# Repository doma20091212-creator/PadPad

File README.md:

#  PadPad
A simple macropad built for stardance mission, consists of 5 key switches, a rotary encoder and uses Seeduino XIAO RP2040.
It utilizies Direct Pins instead of Keyboard Matrix.

## Dimensions

PCB Dimensions: 65mm x 64mm
Case Dimensions: 84.90mm x 84.50mm x 16mm

## BOM

- 5x Cherry MX 1.00u Switches
- 1x Rotary encoder with switch
- 1x Seeduino XIAO RP2040
- PCB Fabrication
- 3D Printing

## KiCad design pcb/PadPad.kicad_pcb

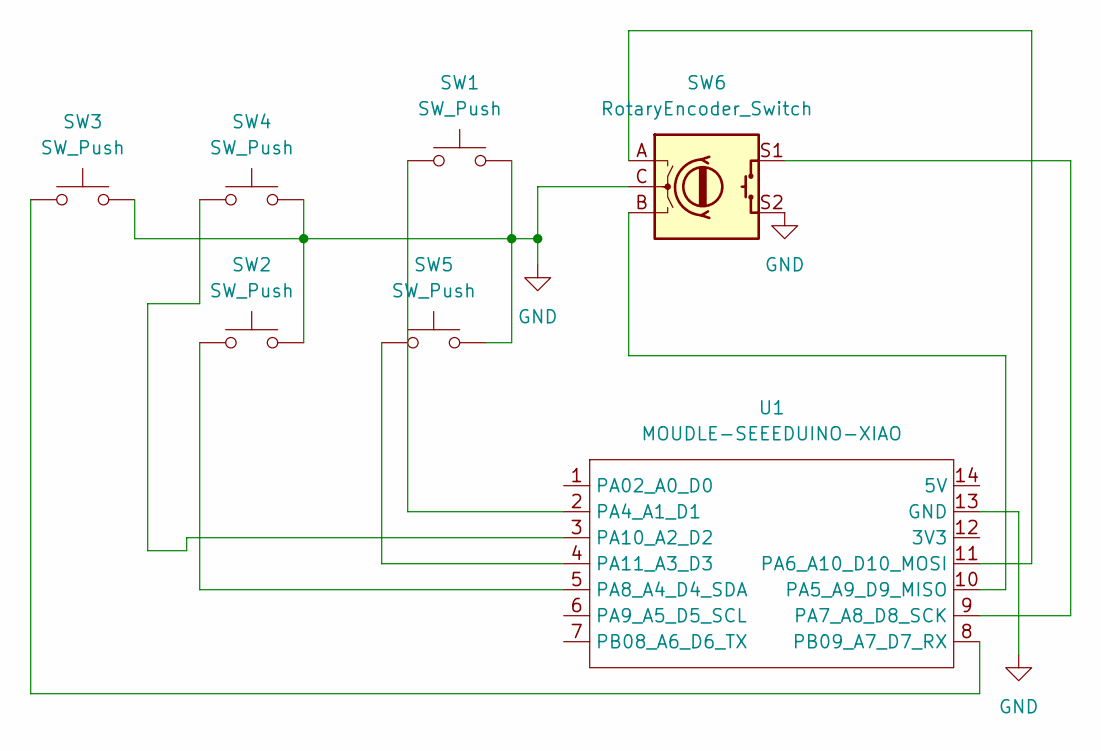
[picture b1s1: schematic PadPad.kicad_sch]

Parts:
SW1, SW2, SW3, SW4, SW5: SW_Push; SW_Cherry_MX_1.00u_PCB
SW6: RotaryEncoder_Switch; RotaryEncoder_Alps_EC11E-Switch_Vertical_H20mm
U1: MOUDLE-SEEEDUINO-XIAO; XIAO-Generic-Hybrid-14P-2.54-21X17.8MM

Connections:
GND: SW1.2, SW2.2, SW3.2, SW4.2, SW5.2, SW6.C, SW6.S2, U1.13 (GND)
unnamed: SW1.1, U1.2 (PA4_A1_D1)
unnamed: SW6.B, U1.10 (PA5_A9_D9_MISO)
unnamed: SW6.A, U1.11 (PA6_A10_D10_MOSI)
unnamed: SW6.S1, U1.9 (PA7_A8_D8_SCK)
unnamed: SW2.1, U1.5 (PA8_A4_D4_SDA)
unnamed: SW4.1, U1.3 (PA10_A2_D2)
unnamed: SW5.1, U1.4 (PA11_A3_D3)
unnamed: SW3.1, U1.8 (PB09_A7_D7_RX)

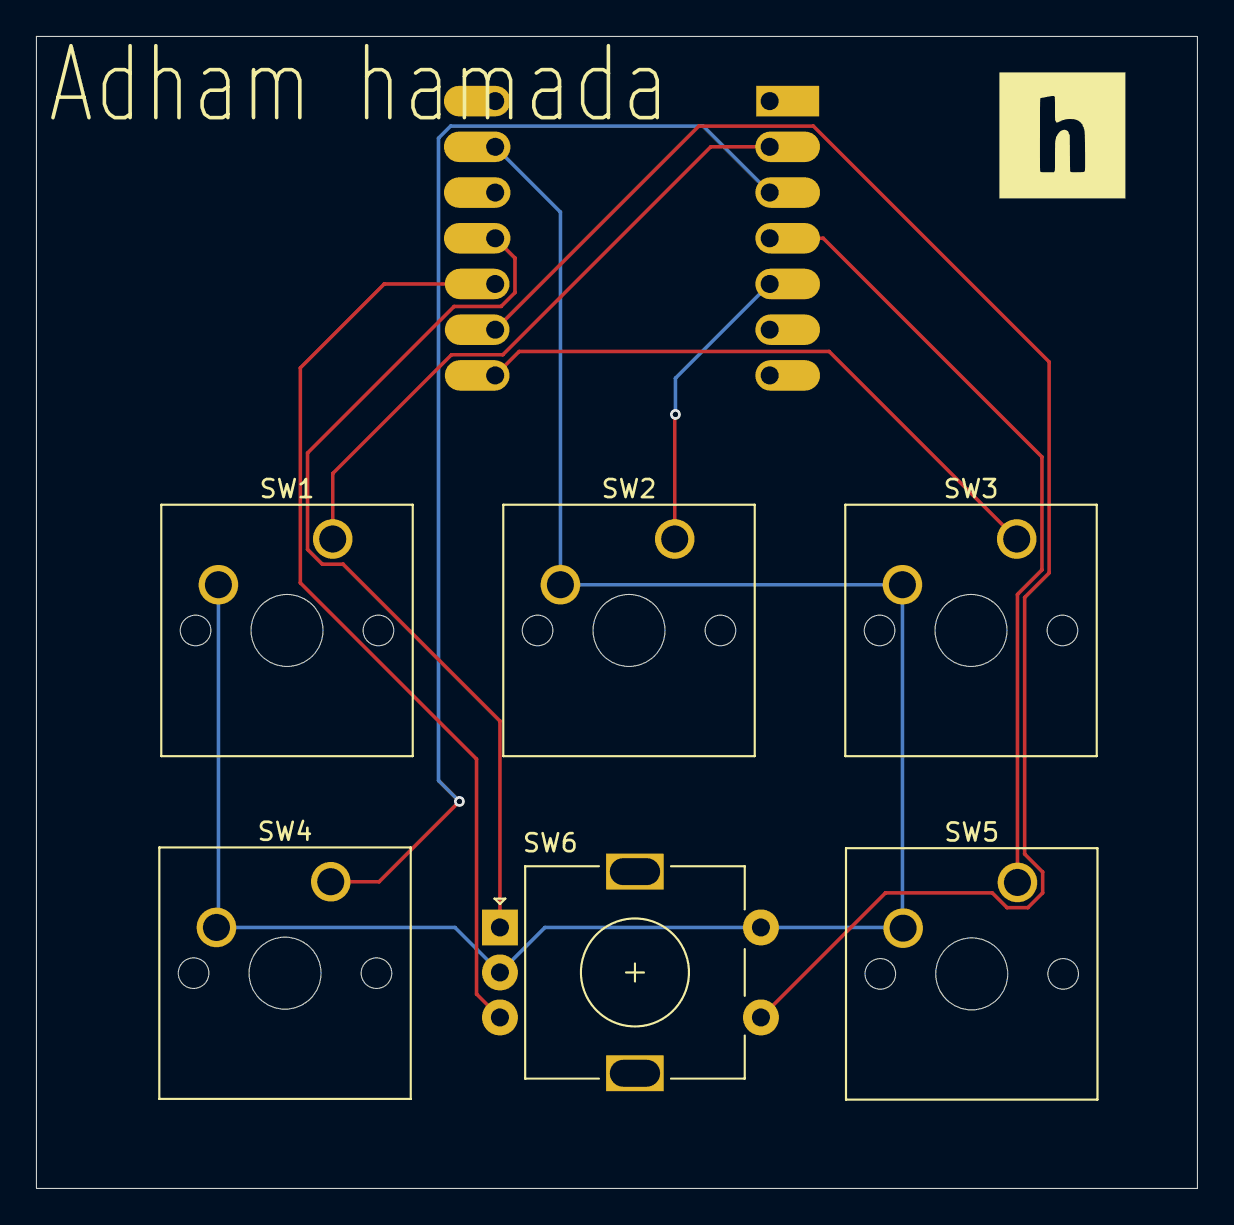
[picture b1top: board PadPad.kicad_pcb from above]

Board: 2 copper layers, 64.5 x 64.0 mm, 7 parts (1 on the bottom side), 9 nets.
